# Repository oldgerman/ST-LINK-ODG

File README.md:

# ST-LINK-ODG

> USB-C口的ST-LINK模块（0603元件100%，易于焊接 ）

ST官方的Nucleo-64板子用ST-LINK有点不方便，前段时间看到稚晖君开源了USB-C口的[ST-Link-Nano](https://github.com/peng-zhihui/ST-Link-Nano)，心血来潮也想做一个，无奈本人手残焊不来0402元件，遂准备做一个0603版本的。以前一直用Eagle，听朋友[稀饭放姜](https://space.bilibili.com/393224264?spm_id_from=333.788.b_765f7570696e666f.1)说Kicad更香，跟着他的[视频教程](https://www.bilibili.com/video/BV12J411z7j7?from=search&seid=1305491858116785113)快速学习了一个，于是整出来了：

## Notice

### PCB工艺参数

- PCB厚度1.6mm，双面板
- 线宽/线距6mil，最小过孔0.3mm，最小阻焊桥>5mil

### 物料

- PCB上有一个3528封装的LED，是红-普绿双色反极的（与ST官方开发板一样），”普绿“就是黄绿色的意思，不要与常见的红-翠绿双色LED混淆（翠绿真心丑还倍儿亮），[推荐购买链接](https://item.taobao.com/item.htm?id=569456631431)，也可以用普通0603 LED代替

- USBLC6-2SC6是USB2.0总线ESD保护器件

- USB D+ 的1.5K上拉电阻经S8050到3.3V，B极由MCU的GPIO控制，与ST的原理图一致没有省

### 跳线

  红色跳线被下载固件，蓝色跳线当ST-LINK

## 焊接测试

> S8050左右脚位反了，待修改，目前反过来焊接S8050能正常使用烧录

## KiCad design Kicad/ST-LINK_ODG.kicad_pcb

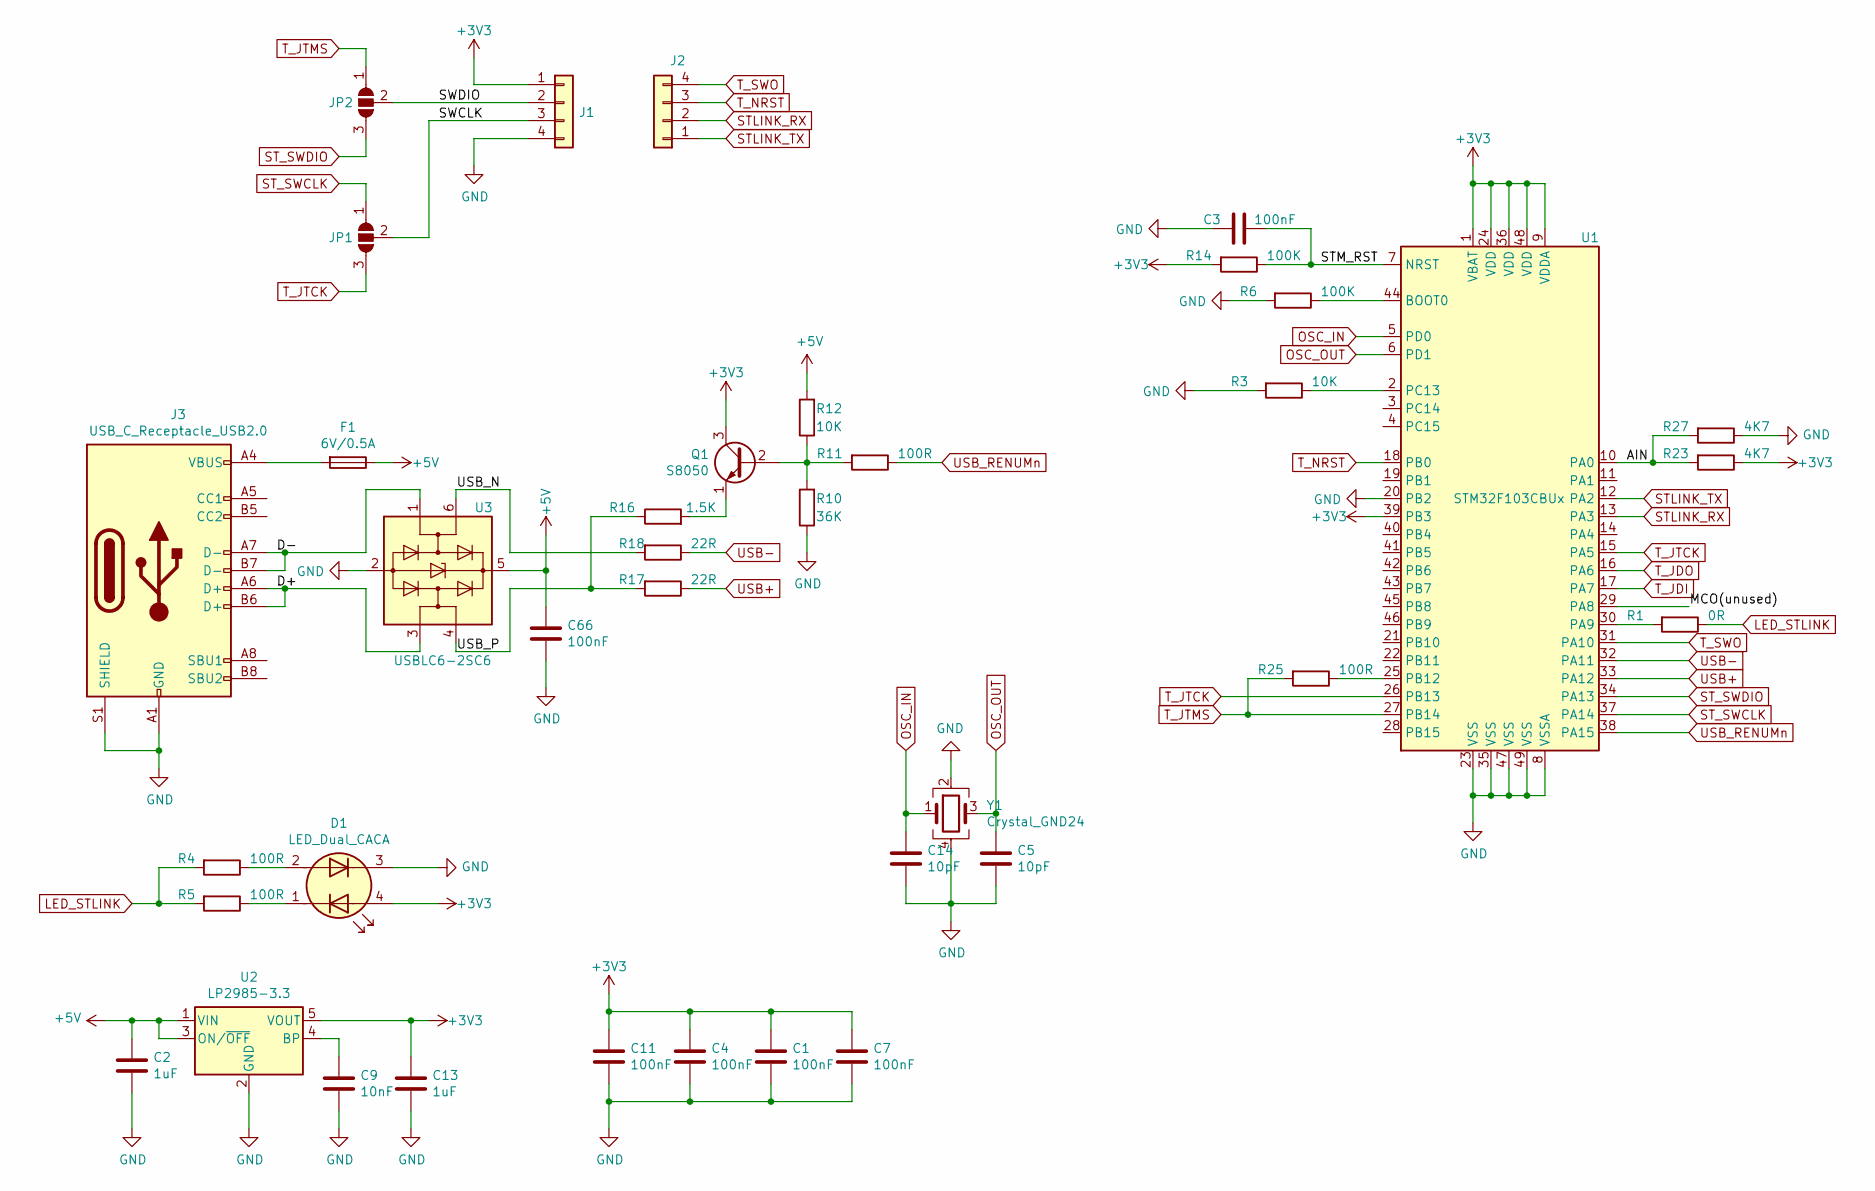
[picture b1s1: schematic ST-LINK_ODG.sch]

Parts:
C1, C3, C4, C7, C11, C66: 100nF; C_0603_1608Metric
C2, C13: 1uF; C_0603_1608Metric
C5, C14: 10pF; C_0603_1608Metric
C9: 10nF; C_0603_1608Metric
D1: LED_Dual_CACA; LED_Cree-PLCC4_3.2x2.8mm_CCW
F1: 6V/0.5A; Fuse_0603_1608Metric
J1, J2: Conn_01x04; PinHeader_1x04_P2.54mm_Horizontal_SMD_PAD_No_Slik
J3: USB_C_Receptacle_USB2.0; USB_C_Receptacle_XKB_U262-16XN-4BVC11_less_Slik
JP1, JP2: SolderJumper_3_Open; SolderJumper-3_Mini_Open_RoundedPad
Q1: S8050; SOT-23
R1: 0R; R_0603_1608Metric
R3, R12: 10K; R_0603_1608Metric
R4, R5, R11, R25: 100R; R_0603_1608Metric
R6, R14: 100K; R_0603_1608Metric
R10: 36K; R_0603_1608Metric
R16: 1.5K; R_0603_1608Metric
R17, R18: 22R; R_0603_1608Metric
R23, R27: 4K7; R_0603_1608Metric
U1: STM32F103CBUx; QFN-48-1EP_7x7mm_P0.5mm_EP5.45x5.45mm
U2: LP2985-3.3; SOT-23-5
U3: USBLC6-2SC6; SOT-23-6
Y1: Crystal_GND24; 3.2X2.5_KX-7

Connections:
+3V3: C1.1, C4.1, C7.1, C11.1, C13.2, D1.4 (K1), J1.1, Q1.3 (C), R14.2, R23.1, U1.1 (VBAT), U1.9 (VDDA), U1.24 (VDD), U1.36 (VDD), U1.39 (PB3), U1.48 (VDD), U2.5 (VOUT)
+5V: C2.1, C66.1, F1.1, R12.2, U2.1 (VIN), U2.3 (ON/~OFF~), U3.5 (VBUS)
/AIN: R23.2, R27.2, U1.10 (PA0)
/D+: J3.A6 (D+), J3.B6 (D+), U3.3 (I/O2)
/D-: J3.A7 (D-), J3.B7 (D-), U3.1 (I/O1)
/MCO(unused): U1.29 (PA8)
/STM_RST: C3.1, R14.1, U1.7 (NRST)
/SWCLK: J1.3, JP1.2 (C)
/SWDIO: J1.2, JP2.2 (C)
/USB_N: R18.2, U3.6 (I/O1)
/USB_P: R16.1, R17.2, U3.4 (I/O2)
GND: C1.2, C2.2, C3.2, C4.2, C5.1, C7.2, C9.1, C11.2, C13.1, C14.1, C66.2, D1.3 (K2), J1.4, J3.A1 (GND), J3.A12 (GND), J3.B1 (GND), J3.B12 (GND), J3.S1 (SHIELD), R3.2, R6.2, R10.1, R27.1, U1.8 (VSSA), U1.20 (PB2), U1.23 (VSS), U1.35 (VSS), U1.47 (VSS), U1.49 (VSS), U2.2 (GND), U3.2 (GND), Y1.2, Y1.4
LED_STLINK: R1.1, R4.2, R5.2
unnamed: C9.2, U2.4 (BP)
unnamed: D1.1 (A1), R5.1
unnamed: D1.2 (A2), R4.1
unnamed: F1.2, J3.A4 (VBUS), J3.A9 (VBUS), J3.B4 (VBUS), J3.B9 (VBUS)
unnamed: Q1.1 (E), R16.2
unnamed: Q1.2 (B), R10.2, R11.2, R12.1
unnamed: R1.2, U1.30 (PA9)
unnamed: R3.1, U1.2 (PC13)
unnamed: R6.1, U1.44 (BOOT0)
unnamed: R25.1, U1.25 (PB12)
OSC_IN: C14.2, U1.5 (PD0), Y1.1
OSC_OUT: C5.2, U1.6 (PD1), Y1.3
STLINK_RX: J2.2, U1.13 (PA3)
STLINK_TX: J2.1, U1.12 (PA2)
ST_SWCLK: JP1.1 (A), U1.37 (PA14)
ST_SWDIO: JP2.3 (B), U1.34 (PA13)
T_JDI: U1.17 (PA7)
T_JDO: U1.16 (PA6)
T_JTCK: JP1.3 (B), U1.15 (PA5), U1.26 (PB13)
T_JTMS: JP2.1 (A), R25.2, U1.27 (PB14)
T_NRST: J2.3, U1.18 (PB0)
T_SWO: J2.4, U1.31 (PA10)
USB+: R17.1, U1.33 (PA12)
USB-: R18.1, U1.32 (PA11)
USB_RENUMn: R11.1, U1.38 (PA15)

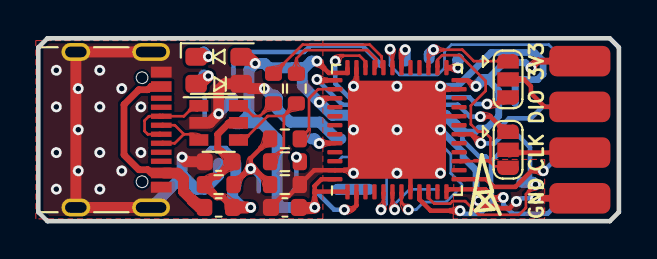
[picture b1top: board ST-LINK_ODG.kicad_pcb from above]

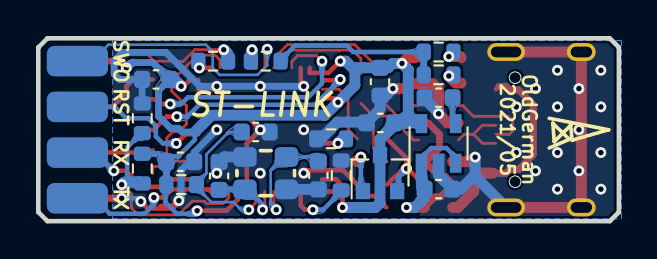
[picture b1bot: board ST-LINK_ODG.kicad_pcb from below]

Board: 2 copper layers, 32.3 x 10.2 mm, 38 parts (22 on the bottom side), 35 nets.

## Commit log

2021-05-26 1st Upload
2021-05-26 2st Upload
